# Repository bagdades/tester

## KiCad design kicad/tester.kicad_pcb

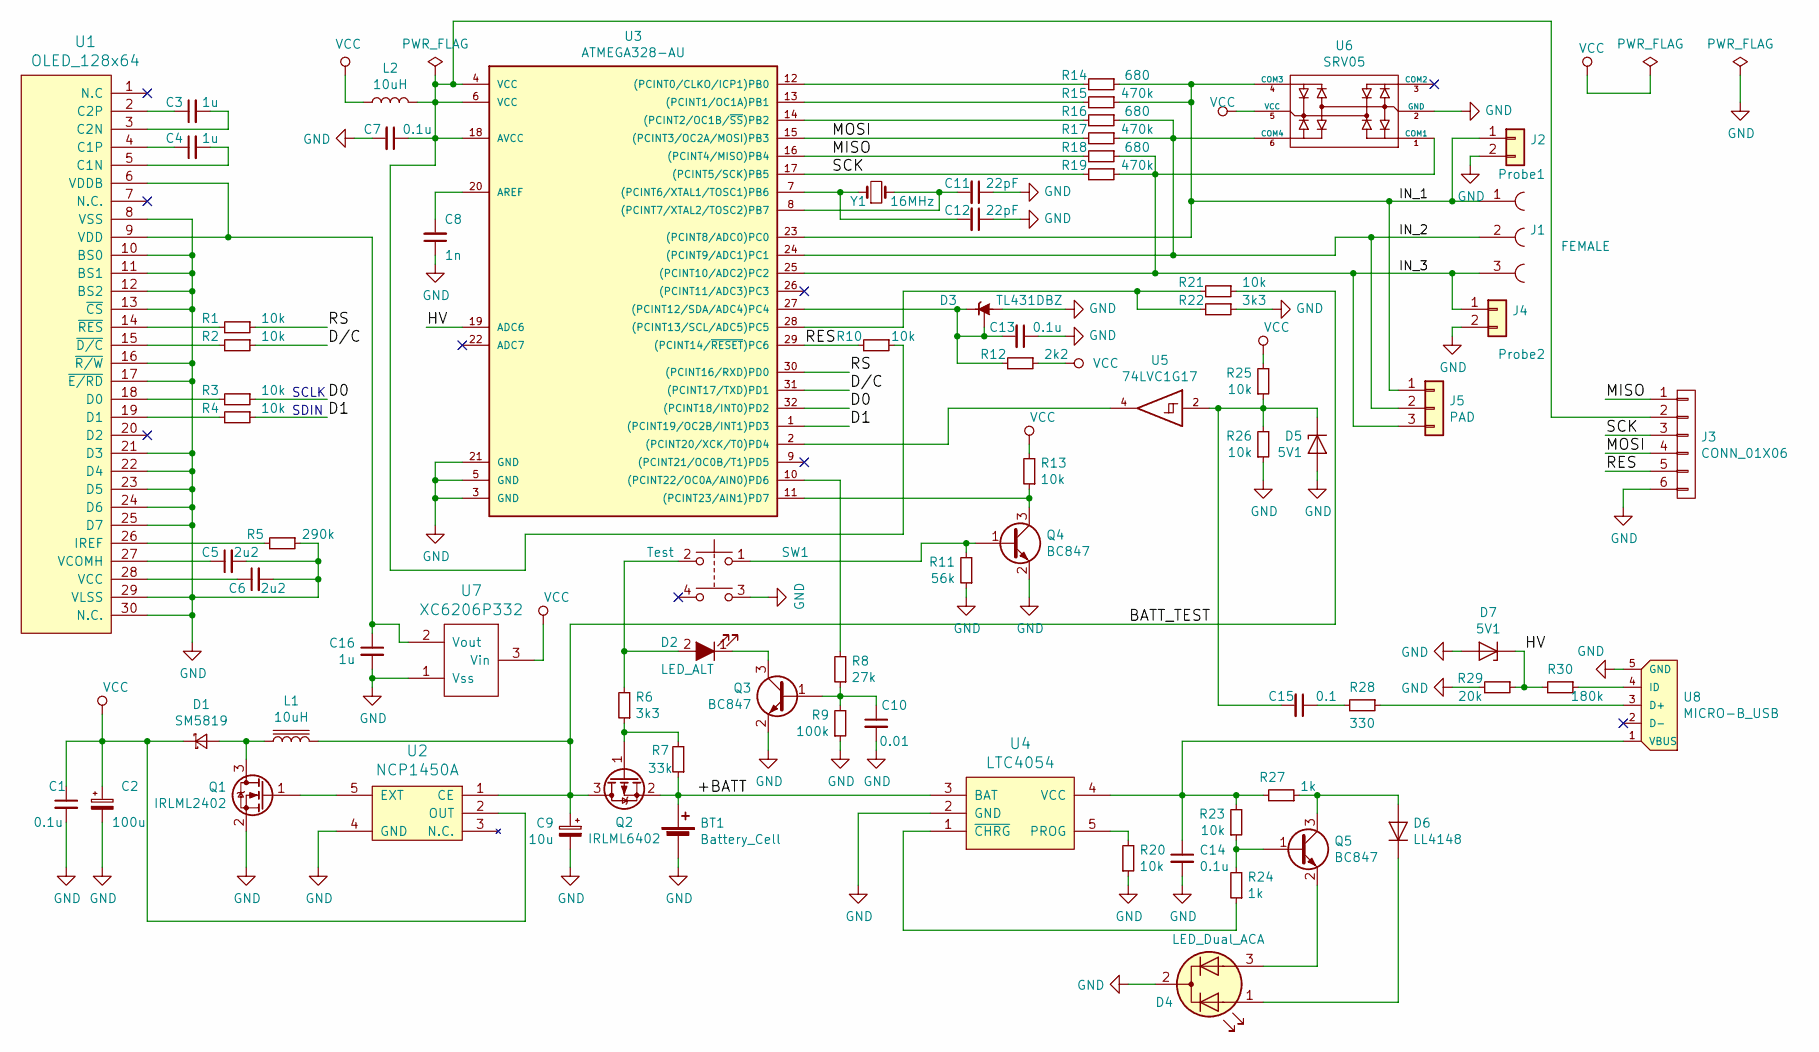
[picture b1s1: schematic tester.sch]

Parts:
BT1: Battery_Cell; PinHeader_1x02_P2.54mm_Vertical
C1, C7, C13, C14: 0.1u; C_0603_1608Metric
C2: 100u; c_tant_B
C3, C4, C16: 1u; C_0603_1608Metric
C5, C6: 2u2; C_0603_1608Metric
C8: 1n; C_0603_1608Metric
C9: 10u; c_tant_A
C10: 0.01; C_0603_1608Metric
C11, C12: 22pF; C_0603_1608Metric
C15: 0.1; C_0603_1608Metric
D1: SM5819; melf
D2: LED_ALT; LED_D3.0mm
D3: TL431DBZ; SOT-23
D4: LED_Dual_ACA; LED_D3.0mm-3
D5, D7: 5V1; D_MiniMELF
D6: LL4148; D_MiniMELF
J1: FEMALE; PinSocket_1x03_P2.54mm_Vertical
J2: Probe1; conn_tester
J3: CONN_01X06; avr_spi
J4: Probe2; conn_tester
J5: PAD; conn_threepoint
L1: 10uH; L_Coilcraft_XAL5030
L2: 10uH; L_0805_2012Metric
Q1: IRLML2402; SOT-23
Q2: IRLML6402; SOT-23
Q3, Q4, Q5: BC847; SOT-23
R1, R2, R3, R4, R10, R13, R20, R21, R23, R25, R26: 10k; R_0603_1608Metric
R5: 290k; R_0603_1608Metric
R6, R22: 3k3; R_0603_1608Metric
R7: 33k; R_0603_1608Metric
R8: 27k; R_0603_1608Metric
R9: 100k; R_0603_1608Metric
R11: 56k; R_0603_1608Metric
R12: 2k2; R_0603_1608Metric
R14, R16, R18: 680; R_1206_3216Metric
R15, R17, R19: 470k; R_1206_3216Metric
R24, R27: 1k; R_0603_1608Metric
R28: 330; R_0603_1608Metric
R29: 20k; R_0603_1608Metric
R30: 180k; R_0603_1608Metric
SW1: Test; BUT6120
U1: OLED_128x64; oled
U2: NCP1450A; SOT-23-5
U3: ATMEGA328-AU; TQFP-32_7x7mm_P0.8mm
U4: LTC4054; SOT-23-5
U5: 74LVC1G17; SOT-23-5
U6: SRV05; SOT-23-6
U7: XC6206P332; SOT-23
U8: MICRO-B_USB; USB_Micro-B_Molex_47346-0001
Y1: 16MHz; crystal_hc-49s

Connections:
/+BATT: BT1.1 (+), Q2.2 (S), R7.1, U4.3 (BAT)
/BATT_TEST: C9.1, L1.2, Q2.3 (D), R21.1, U2.1 (CE)
/D0: R3.1, U3.32 ((PCINT18/INT0)PD2)
/D1: R4.1, U3.1 ((PCINT19/OC2B/INT1)PD3)
/D/C: R2.1, U3.31 ((PCINT17/TXD)PD1)
/HV: D7.1 (K), R29.1, R30.2, U3.19 (ADC6)
/IN_1: J1.1, J2.1, J5.1, R14.1, R15.1, U3.23 ((PCINT8/ADC0)PC0), U6.4 (COM3)
/IN_2: J1.2, J5.2, R16.1, R17.1, U3.24 ((PCINT9/ADC1)PC1), U6.6 (COM4)
/IN_3: J1.3, J4.1, J5.3, R18.1, R19.1, U3.25 ((PCINT10/ADC2)PC2), U6.1 (COM1)
/MISO: J3.1, R18.2, U3.16 ((PCINT4/MISO)PB4)
/MOSI: J3.4, R17.2, U3.15 ((PCINT3/OC2A/MOSI)PB3)
/RES: J3.5, R10.2, U3.29 ((PCINT14/~RESET~)PC6)
/RS: R1.1, U3.30 ((PCINT16/RXD)PD0)
/SCK: J3.3, R19.2, U3.17 ((PCINT5/SCK)PB5)
GND: BT1.2 (-), C1.2, C2.2, C5.2, C6.2, C7.2, C8.1, C9.2, C10.2, C11.1, C12.1, C13.1, C14.2, C16.2, D3.3 (A), D4.2 (K), D5.2 (A), D7.2 (A), J2.2, J3.6, J4.2, Q1.2 (S), Q3.2 (E), Q4.2 (E), R5.1, R9.1, R11.1, R20.1, R22.1, R26.1, R29.2, SW1.3, U1.8 (VSS), U1.10 (BS0), U1.11 (BS1), U1.12 (BS2), U1.13 (~CS), U1.16 (~R/W), U1.17 (~E/RD), U1.21 (D3), U1.22 (D4), U1.23 (D5), U1.24 (D6), U1.25 (D7), U1.29 (VLSS), U1.30 (N.C.), U2.4 (GND), U3.3 (GND), U3.5 (GND), U3.21 (GND), U4.2 (GND), U5.3 (GND), U6.2 (GND), U7.1 (Vss), U8.5 (GND)
unnamed: C3.1, U1.2 (C2P)
unnamed: C3.2, U1.3 (C2N)
unnamed: C4.1, U1.4 (C1P)
unnamed: C4.2, U1.5 (C1N)
unnamed: C5.1, U1.27 (VCOMH)
unnamed: C6.1, U1.28 (VCC)
unnamed: C7.1, J3.2, L2.2, R10.1, U3.4 (VCC), U3.6 (VCC), U3.18 (AVCC)
unnamed: C8.2, U3.20 (AREF)
unnamed: C10.1, Q3.1 (B), R8.1, R9.2
unnamed: C11.2, U3.8 ((PCINT7/XTAL2/TOSC2)PB7), Y1.2
unnamed: C12.2, U3.7 ((PCINT6/XTAL1/TOSC1)PB6), Y1.1
unnamed: C13.2, D3.1 (K), D3.2 (REF), R12.2, U3.27 ((PCINT12/SDA/ADC4)PC4)
unnamed: C14.1, R23.2, R27.2, U4.4 (VCC), U8.1 (VBUS)
unnamed: C15.1, R28.2
unnamed: C15.2, D5.1 (K), R25.1, R26.2, U5.2
unnamed: C16.1, U1.6 (VDDB), U1.9 (VDD), U7.2 (Vout)
unnamed: D1.2 (A), L1.1, Q1.3 (D)
unnamed: D2.1 (K), Q3.3 (C)
unnamed: D2.2 (A), R6.2, SW1.2
unnamed: D4.1 (A1), D6.1 (K)
unnamed: D4.3 (A2), Q5.2 (E)
unnamed: D6.2 (A), Q5.3 (C), R27.1
unnamed: Q1.1 (G), U2.5 (EXT)
unnamed: Q2.1 (G), R6.1, R7.2
unnamed: Q4.1 (B), R11.2, SW1.1
unnamed: Q4.3 (C), R13.1, U3.11 ((PCINT23/AIN1)PD7)
unnamed: Q5.1 (B), R23.1, R24.2
unnamed: R1.2, U1.14 (~RES)
unnamed: R2.2, U1.15 (~D/C)
unnamed: R3.2, U1.18 (D0)
unnamed: R4.2, U1.19 (D1)
unnamed: R5.2, U1.26 (IREF)
unnamed: R8.2, U3.10 ((PCINT22/OC0A/AIN0)PD6)
unnamed: R14.2, U3.12 ((PCINT0/CLKO/ICP1)PB0)
unnamed: R15.2, U3.13 ((PCINT1/OC1A)PB1)
unnamed: R16.2, U3.14 ((PCINT2/OC1B/~SS~)PB2)
unnamed: R20.2, U4.5 (PROG)
unnamed: R21.2, R22.2, U3.28 ((PCINT13/SCL/ADC5)PC5)
unnamed: R24.1, U4.1 (~CHRG)
unnamed: R28.1, U8.3 (D+)
unnamed: R30.1, U8.4 (ID)
unnamed: U3.2 ((PCINT20/XCK/T0)PD4), U5.4
VCC: C1.1, C2.1, D1.1 (K), L2.1, R12.1, R13.2, R25.2, U2.2 (OUT), U5.5 (VCC), U6.5 (VCC), U7.3 (Vin)

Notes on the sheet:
SCLK
SDIN

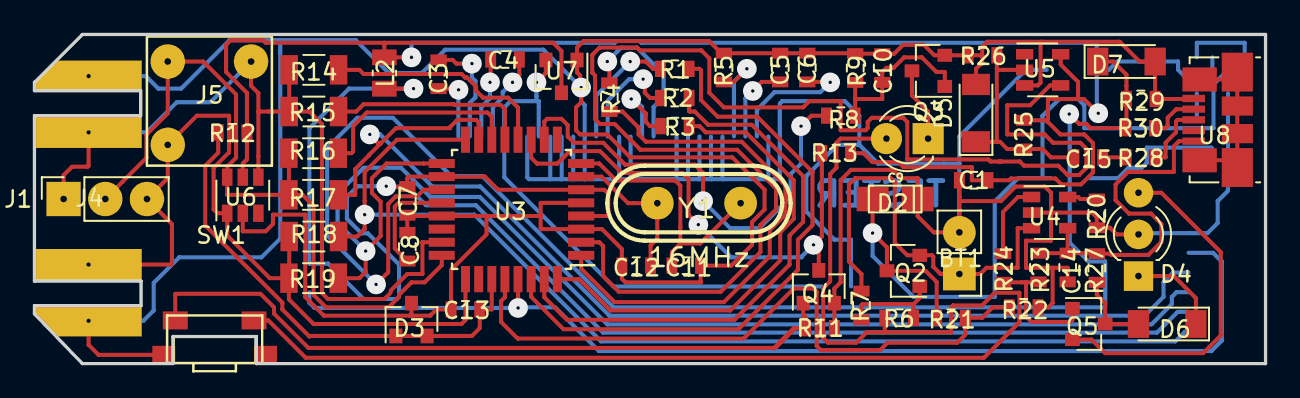
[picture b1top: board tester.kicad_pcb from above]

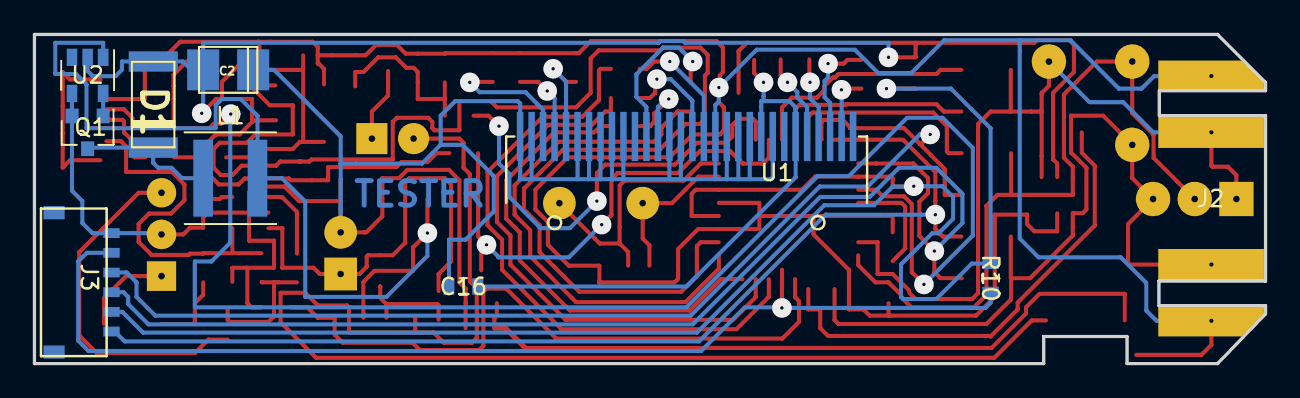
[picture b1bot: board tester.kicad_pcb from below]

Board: 2 copper layers, 75.1 x 20.1 mm, 76 parts (10 on the bottom side), 58 nets.

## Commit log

2017-04-09 First add
2017-04-09 Add other files
2017-04-10 Change package some resistors
2017-04-11 Add footprint oled
2017-04-28 Update pcb
2017-06-05 Start pcb routing
2017-06-08 Change to92 3d settings
2017-06-08 Continue work with pcb
2017-06-14 Correction pcb on work
2017-11-09 Working with pcb
2018-03-19 Recovery pdb start
2018-03-31 Prefinal PCB
2018-04-01 Final PCB
2018-04-10 Final correct and output
2019-06-16 Firmware
2019-06-30 Add work firmware
